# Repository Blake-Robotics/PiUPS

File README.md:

# PiUPS
Project to manage the power supply for the electronics of the robot. A microcontroller is used to monitor the state of the battery and external power inputs.

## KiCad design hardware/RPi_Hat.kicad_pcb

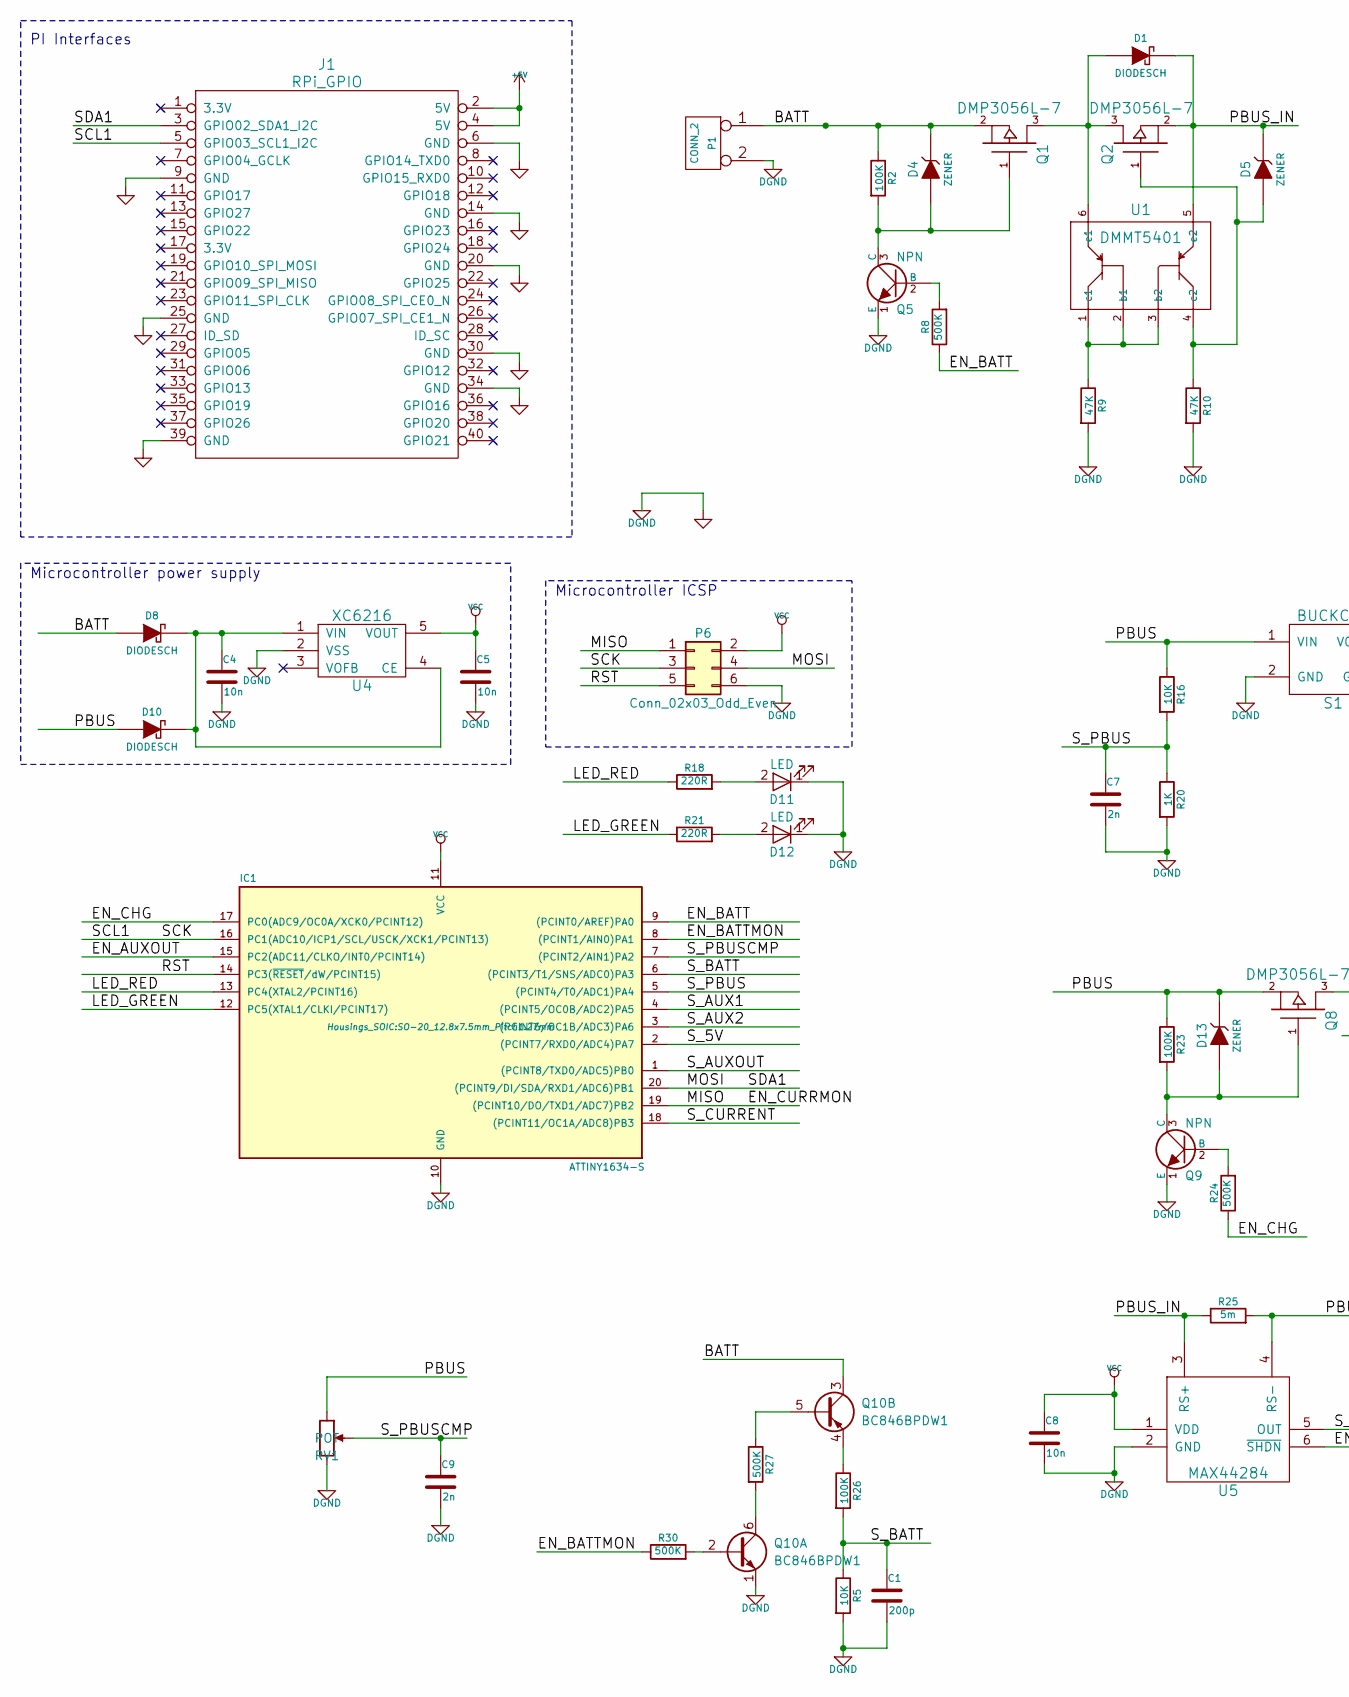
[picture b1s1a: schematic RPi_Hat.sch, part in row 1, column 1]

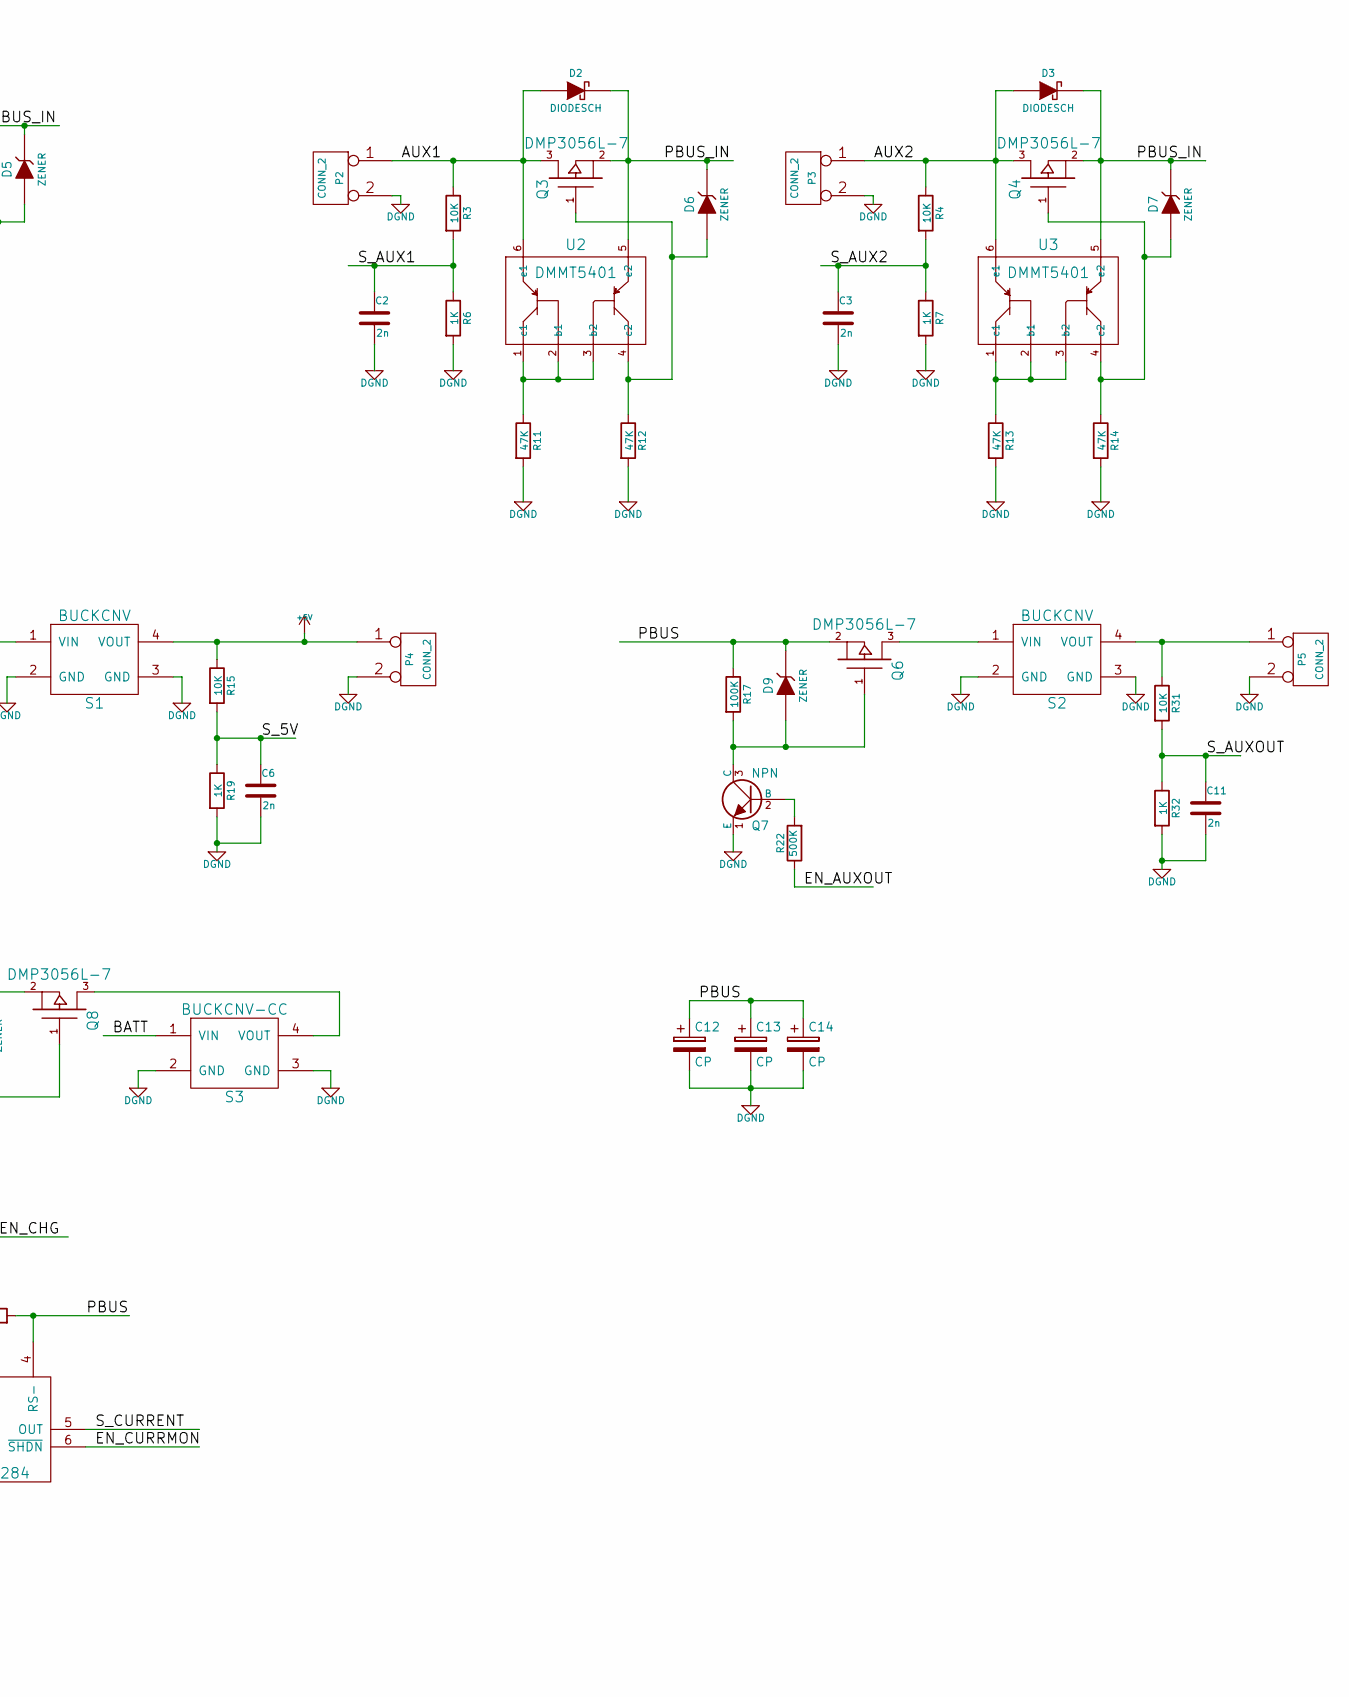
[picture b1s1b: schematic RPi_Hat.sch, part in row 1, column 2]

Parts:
C1: 200p; C_0805_HandSoldering
C2, C3, C6, C7, C9, C11: 2n; C_0805_HandSoldering
C4, C5, C8: 10n; C_0805_HandSoldering
C12, C13, C14: CP; CP_Radial_D8.0mm_P3.50mm
D1, D2, D3, D8, D10: DIODESCH; D_SMA_Handsoldering
D4, D5, D6, D7, D9, D13: ZENER; D_SOD-123F
D11, D12: LED; D_0805
IC1: ATTINY1634-S; SO-20_12.8x7.5mm_Pitch1.27mm
J1: RPi_GPIO
P1, P2, P3, P4, P5: CONN_2; Molex_KK-6410-02_02x2.54mm_Straight
P6: Conn_02x03_Odd_Even; Header_2x03
Q1, Q2, Q3, Q4, Q6, Q8: DMP3056L-7; SOT-23_Handsoldering
Q5, Q7, Q9: NPN; SOT-23_Handsoldering
Q10: BC846BPDW1; SOT-363_SC-70-6_Handsoldering
R2, R17, R23, R26: 100K; R_0805_HandSoldering
R3, R4, R5, R15, R16, R31: 10K; R_0805_HandSoldering
R6, R7, R19, R20, R32: 1K; R_0805_HandSoldering
R8, R22, R24, R27, R30: 500K; R_0805_HandSoldering
R9, R10, R11, R12, R13, R14: 47K; R_0805_HandSoldering
R18, R21: 220R; R_0805_HandSoldering
R25: 5m; R_0805_HandSoldering
RV1: POT; Potentiometer_Trimmer_Bourns_PV36W
S1, S2: BUCKCNV; BUCK
S3: BUCKCNV-CC; Molex_KK-6410-04_04x2.54mm_Straight
U1, U2, U3: DMMT5401; SOT-23-6_Handsoldering
U4: XC6216; SOT-23-5_HandSoldering
U5: MAX44284; SOT-23-6_Handsoldering

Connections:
+5V: J1.2 (5V), J1.4 (5V), P4.1, R15.1, S1.4 (VOUT)
/AUX1: D2.2 (A), P2.1, Q3.3 (D), R3.1, U2.6 (e1)
/AUX2: D3.2 (A), P3.1, Q4.3 (D), R4.1, U3.6 (e1)
/BATT: D4.1 (K), D8.2 (A), P1.1, Q1.2 (S), Q10.3 (C2), R2.1, S3.1 (VIN)
/EN_AUXOUT: IC1.15 (PC2(ADC11/CLKO/INT0/PCINT14)), R22.1
/EN_BATT: IC1.9 ((PCINT0/AREF)PA0), R8.1
/EN_BATTMON: IC1.8 ((PCINT1/AIN0)PA1), R30.1
/EN_CHG: IC1.17 (PC0(ADC9/OC0A/XCK0/PCINT12)), R24.1
/EN_CURRMON: IC1.19 ((PCINT10/DO/TXD1/ADC7)PB2), P6.1, U5.6 (~SHDN)
/LED_GREEN: IC1.12 (PC5(XTAL1/CLKI/PCINT17)), R21.1
/LED_RED: IC1.13 (PC4(XTAL2/PCINT16)), R18.1
/MOSI: IC1.20 ((PCINT9/DI/SDA/RXD1/ADC6)PB1), J1.3 (GPIO02_SDA1_I2C), P6.4
/PBUS: C12.1, C13.1, C14.1, D9.1 (K), D10.2 (A), D13.1 (K), Q6.2 (S), Q8.2 (S), R16.1, R17.1, R23.1, R25.2, RV1.1, S1.1 (VIN), U5.4 (RS-)
/PBUS_IN: D1.1 (K), D2.1 (K), D3.1 (K), D5.1 (K), D6.1 (K), D7.1 (K), Q2.2 (S), Q3.2 (S), Q4.2 (S), R25.1, U1.5 (e2), U2.5 (e2), U3.5 (e2), U5.3 (RS+)
/RST: IC1.14 (PC3(~RESET~/dW/PCINT15)), P6.5
/SCK: IC1.16 (PC1(ADC10/ICP1/SCL/USCK/XCK1/PCINT13)), J1.5 (GPIO03_SCL1_I2C), P6.3
/S_5V: C6.1, IC1.2 ((PCINT7/RXD0/ADC4)PA7), R15.2, R19.1
/S_AUX1: C2.1, IC1.4 ((PCINT5/OC0B/ADC2)PA5), R3.2, R6.1
/S_AUX2: C3.1, IC1.3 ((PCINT6/OC1B/ADC3)PA6), R4.2, R7.1
/S_AUXOUT: C11.1, IC1.1 ((PCINT8/TXD0/ADC5)PB0), R31.2, R32.1
/S_BATT: C1.1, IC1.6 ((PCINT3/T1/SNS/ADC0)PA3), R5.1, R26.2
/S_CURRENT: IC1.18 ((PCINT11/OC1A/ADC8)PB3), U5.5 (OUT)
/S_PBUS: C7.1, IC1.5 ((PCINT4/T0/ADC1)PA4), R16.2, R20.1
/S_PBUSCMP: C9.1, IC1.7 ((PCINT2/AIN1)PA2), RV1.2
DGND: C1.2, C2.2, C3.2, C4.2, C5.2, C6.2, C7.2, C8.2, C9.2, C11.2, C12.2, C13.2, C14.2, D11.1 (K), D12.1 (K), IC1.10 (GND), J1.6 (GND), J1.9 (GND), J1.14 (GND), J1.20 (GND), J1.25 (GND), J1.30 (GND), J1.34 (GND), J1.39 (GND), P1.2 (PM), P2.2 (PM), P3.2 (PM), P4.2 (PM), P5.2 (PM), P6.6, Q5.1 (E), Q7.1 (E), Q9.1 (E), Q10.1 (E1), R5.2, R6.2, R7.2, R9.2, R10.2, R11.2, R12.2, R13.2, R14.2, R19.2, R20.2, R32.2, RV1.3, S1.2 (GND), S1.3 (GND), S2.2 (GND), S2.3 (GND), S3.2 (GND), S3.3 (GND), U4.2 (VSS), U5.2 (GND)
unnamed: C4.1, D8.1 (K), D10.1 (K), U4.1 (VIN), U4.4 (CE)
unnamed: D1.2 (A), Q1.3 (D), Q2.3 (D), U1.6 (e1)
unnamed: D4.2 (A), Q1.1 (G), Q5.3 (C), R2.2
unnamed: D5.2 (A), Q2.1 (G), R10.1, U1.4 (c2)
unnamed: D6.2 (A), Q3.1 (G), R12.1, U2.4 (c2)
unnamed: D7.2 (A), Q4.1 (G), R14.1, U3.4 (c2)
unnamed: D9.2 (A), Q6.1 (G), Q7.3 (C), R17.2
unnamed: D11.2 (A), R18.2
unnamed: D12.2 (A), R21.2
unnamed: D13.2 (A), Q8.1 (G), Q9.3 (C), R23.2
unnamed: P5.1, R31.1, S2.4 (VOUT)
unnamed: Q5.2 (B), R8.2
unnamed: Q6.3 (D), S2.1 (VIN)
unnamed: Q7.2 (B), R22.2
unnamed: Q8.3 (D), S3.4 (VOUT)
unnamed: Q9.2 (B), R24.2
unnamed: Q10.2 (B1), R30.2
unnamed: Q10.4 (E2), R26.1
unnamed: Q10.5 (B2), R27.1
unnamed: Q10.6 (C1), R27.2
unnamed: R9.1, U1.1 (c1), U1.2 (b1), U1.3 (b2)
unnamed: R11.1, U2.1 (c1), U2.2 (b1), U2.3 (b2)
unnamed: R13.1, U3.1 (c1), U3.2 (b1), U3.3 (b2)
VCC: C5.1, C8.1, IC1.11 (VCC), P6.2, U4.5 (VOUT), U5.1 (VDD)

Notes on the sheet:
Microcontroller power supply
Microcontroller ICSP
PI Interfaces

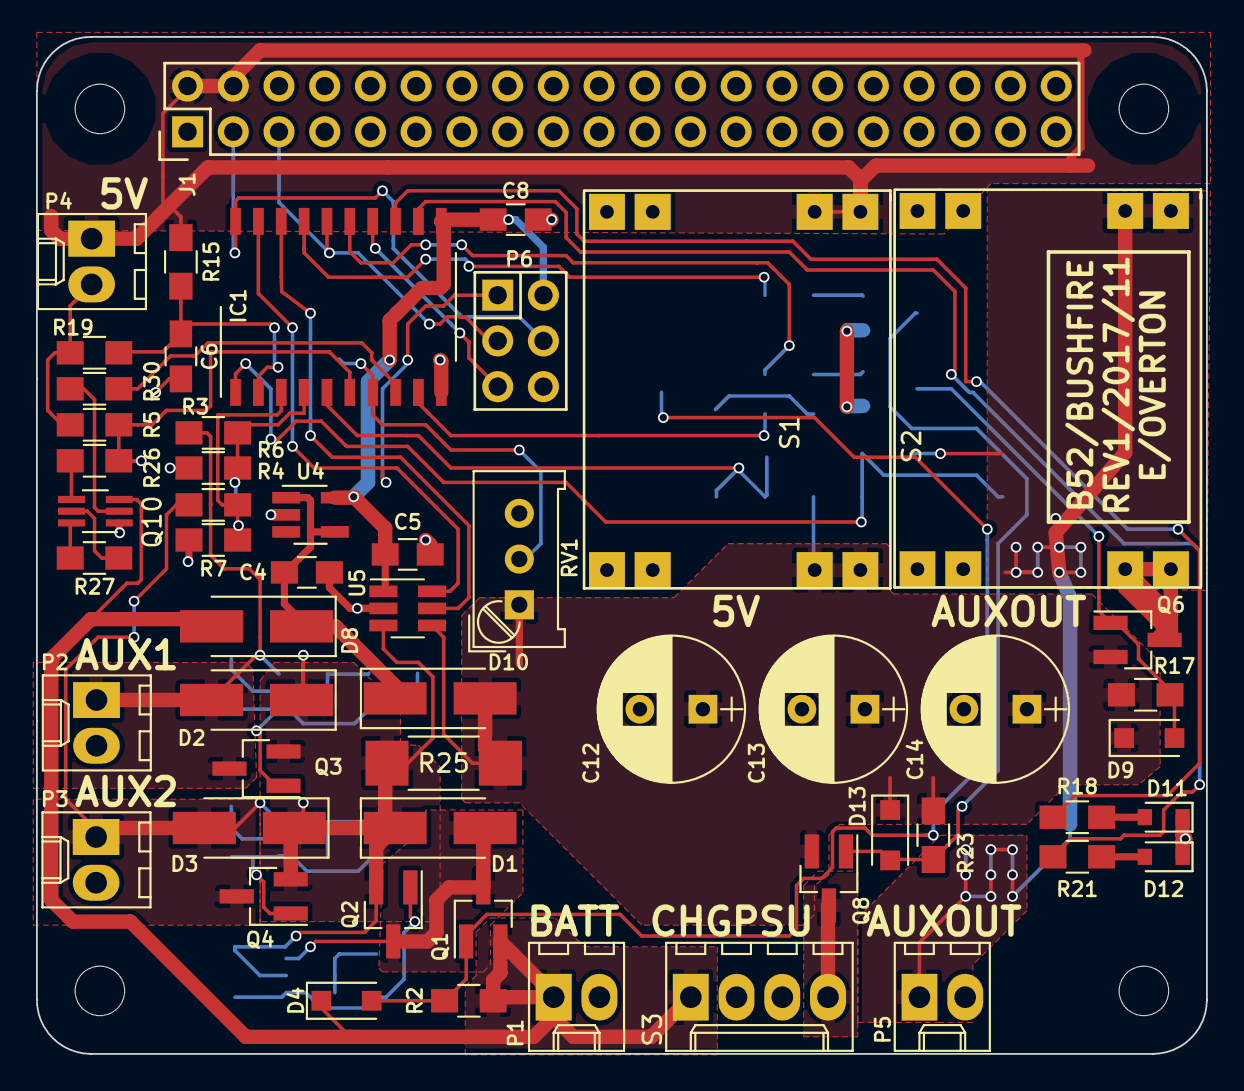
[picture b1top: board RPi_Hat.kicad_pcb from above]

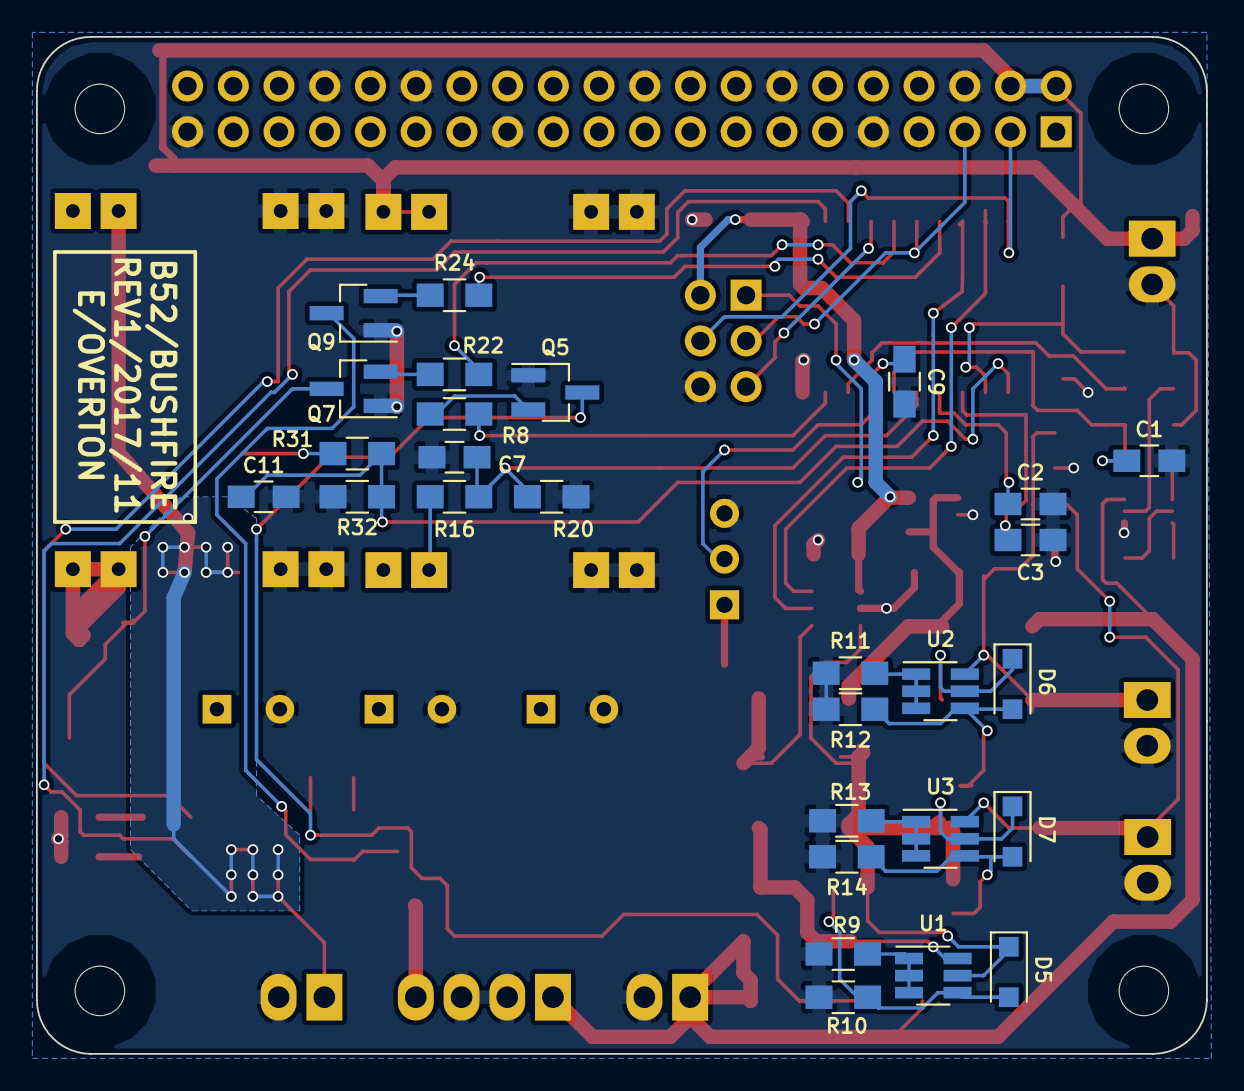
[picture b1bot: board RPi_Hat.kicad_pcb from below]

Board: 2 copper layers, 65.0 x 56.5 mm, 82 parts (28 on the bottom side), 49 nets.

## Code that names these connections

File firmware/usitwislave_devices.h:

/*
Copyright: Erik Slagter <erik@slagter.name>
License: GPLv2

Derived from works by:
	Atmel (Application note 312, licensing unknown, probably public domain)
	Donald R. Blake (licensing unknown, probably public domain)
*/

#if		defined(__AVR_ATtiny2313__)
#	define DDR_USI				DDRB
#	define PORT_USI				PORTB
#	define PIN_USI				PINB
#	define PORT_USI_SDA			PB5
#	define PORT_USI_SCL			PB7
#	define PIN_USI_SDA			PINB5
#	define PIN_USI_SCL			PINB7
#	define USI_OVERFLOW_VECTOR	USI_OVERFLOW_vect
#endif

#if		defined(__AVR_ATtiny1634__)
#	define DDR_SDA_USI			DDRB
#	define PORT_SDA_USI			PORTB
#	define PIN_SDA_USI			PINB
#	define PORT_USI_SDA			PB1
#	define PIN_USI_SDA			PINB1
#   define DDR_SCL_USI          DDRC
#   define PORT_SCL_USI         PORTC
#   define PIN_SCL_USI          PINC
#	define PORT_USI_SCL			PC1
#	define PIN_USI_SCL			PINC1
#	define USI_OVERFLOW_VECTOR	USI_OVERFLOW_vect
#endif

#if		defined(__AVR_ATtiny24__) | \
		defined(__AVR_ATtiny44__) | \
		defined(__AVR_ATtiny84__)
#	define DDR_USI				DDRA
#	define PORT_USI				PORTA
#	define PIN_USI				PINA
#	define PORT_USI_SDA			PA6
#	define PORT_USI_SCL			PA4
#	define PIN_USI_SDA			PINA6
#	define PIN_USI_SCL			PINA4
#	define USI_OVERFLOW_VECTOR	USI_OVF_vect
#endif

#if		defined(__AVR_ATtiny25__) | \
		defined(__AVR_ATtiny45__) | \
		defined(__AVR_ATtiny85__)
#	define DDR_USI				DDRB
#	define PORT_USI				PORTB
#	define PIN_USI				PINB
#	define PORT_USI_SDA			PB0
#	define PORT_USI_SCL			PB2
#	define PIN_USI_SDA			PINB0
#	define PIN_USI_SCL			PINB2
#	define USI_OVERFLOW_VECTOR	USI_OVF_vect
#endif

#if defined(__AVR_ATtiny26__)
#	define DDR_USI				DDRB
#	define PORT_USI				PORTB
#	define PIN_USI				PINB
#	define PORT_USI_SDA			PB0
#	define PORT_USI_SCL			PB2
#	define PIN_USI_SDA			PINB0
#	define PIN_USI_SCL			PINB2
#	define USI_OVERFLOW_VECTOR	USI_OVF_vect
#endif

#if		defined(__AVR_ATtiny261__) | \
		defined(__AVR_ATtiny261a__) | \
		defined(__AVR_ATtiny461__) | \
		defined(__AVR_ATtiny461a__) | \
		defined(__AVR_ATtiny861__) | \
		defined(__AVR_ATtiny861a__)
#	if		defined(USI_ON_PORT_A)
#		define DDR_USI				DDRA
#		define PORT_USI				PORTA
#		define PIN_USI				PINA
#		define PORT_USI_SDA			PA0
#		define PORT_USI_SCL			PA2
#		define PIN_USI_SDA			PINA0
#		define PIN_USI_SCL			PINA2
#	else
#		define DDR_USI				DDRB
#		define PORT_USI				PORTB
#		define PIN_USI				PINB
#		define PORT_USI_SDA			PB0
#		define PORT_USI_SCL			PB2
#		define PIN_USI_SDA			PINB0
#		define PIN_USI_SCL			PINB2
#	endif
#	define USI_OVERFLOW_VECTOR		USI_OVF_vect
#endif

#if		defined(__AVR_ATmega165__) | \
		defined(__AVR_ATmega325__) | \
		defined(__AVR_ATmega3250__) | \
		defined(__AVR_ATmega645__) | \
		defined(__AVR_ATmega6450__) | \
		defined(__AVR_ATmega329__) | \
		defined(__AVR_ATmega3290__)
#	define DDR_USI				DDRE
#	define PORT_USI				PORTE
#	define PIN_USI				PINE
#	define PORT_USI_SDA			PE5
#	define PORT_USI_SCL			PE4
#	define PIN_USI_SDA			PINE5
#	define PIN_USI_SCL			PINE4
#	define USI_OVERFLOW_VECTOR	USI_OVERFLOW_vect
#endif

#if defined(__AVR_ATmega169__)
#	define DDR_USI				DDRE
#	define PORT_USI				PORTE
#	define PIN_USI				PINE
#	define PORT_USI_SDA			PE5
#	define PORT_USI_SCL			PE4
#	define PIN_USI_SDA			PINE5
#	define PIN_USI_SCL			PINE4
#	define USI_OVERFLOW_VECTOR	USI_OVERFLOW_vect
#endif

#ifndef DDR_SCL_USI
#	define DDR_SDA_USI			DDR_USI
#	define PORT_SDA_USI			PORT_USI
#	define PIN_SDA_USI			PIN_USI
#   define DDR_SCL_USI          DDR_USI
#	define PORT_USI_SDA			PORT_USI
#	define PIN_USI_SDA			PIN_USI
#endif

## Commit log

2017-09-15 Initial commit of firmware
2017-09-15 Added licence info to usi twi interface
2017-09-15 Extended ADC to cover all channels, and now load resistor divider values from the eeprom, which can be set over i2c.
2017-09-15 Initial commit of some software for communicating with the microcontroller over I2C on the PI
2017-09-15 Corrections
2017-09-19 Added current status to return power source
2017-09-19 Split I2C access to seperate tools, which need integrating with make and testing
2017-09-21 Updates to add i2ctools to makefile, and to use them in i2ctest
2017-09-22 Added dedicated source files for PiUPS tools
2017-09-25 Adding doxygen documentation
2017-09-25 Update to doxyfile to make recursive documentation
2017-09-25 Added simple VCC read function
2017-09-30 Added Status decoding functionality
2017-10-01 Extended documentation
2017-10-01 Added a configuration program to set configuration parameters stored in the EEPROM of the Micro
2017-10-22 Adding 5V rail voltage sensor
2017-10-28 Extended software to read 5v rail
2017-10-31 Beginning schematic to make a hat
2017-11-02 Almost finished schematic
2017-11-12 Semi finished pcb
2017-11-15 First PCB version
2017-11-15 Added solder masks to gerbers
2017-11-17 BOM Updates for Rev1
2017-11-26 Updates to firmware code for ATTINY1634, not complete
2017-11-26 Support for extra sensors
2017-11-26 Properly working with conversion constants
2017-11-30 Work on enable signals
2017-12-06 Extensions to I2C registers
2017-12-06 Extended registers and fixed bug in power source detection
2017-12-06 Extensions to SW configuration
2017-12-07 Added power saving to program
2018-01-10 Cleanup of mistakenly committed binaries
2018-01-10 Adding a logging application
2018-01-17 Fix to enable battery charging in firmware
2018-01-17 Force log file to be flushed to disk after each log
